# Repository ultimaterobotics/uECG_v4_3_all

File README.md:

# uECG
uECG - very small wearable ECG device that sends raw and processed data over BLE

**This is an old repository - new version is located here: https://github.com/ultimaterobotics/uECG (and is divided into multiple repositories for relevant parts of the project, links are in description)**

Project is in active development stage, at the current moment we have shared:
 * schematics and PCB design
 * ECG monitor program based on Node.js, cross-platform
 * ECG monitor program for Linux (outdated: might not work properly, please use cross-platform version instead)
 * Firmware for the main unit, rather stable and reliable build. Next planned major update will cover better beat detection and more robust bpm processing. 
 * Firmware for the base unit that supports uploading uECG firmware via radio
 * Android app with major rework, quite stable now
 * bootloader code for USB base station: supports base firmware update via USB without the need of STLink programmer
 * bootloader code for uECG device: supports firmware update via radio (requires base with new firmware, old base firmware doesn't support this function)

You can follow the project on Hackaday: https://hackaday.io/project/164486-uecg-a-very-small-wearable-ecg

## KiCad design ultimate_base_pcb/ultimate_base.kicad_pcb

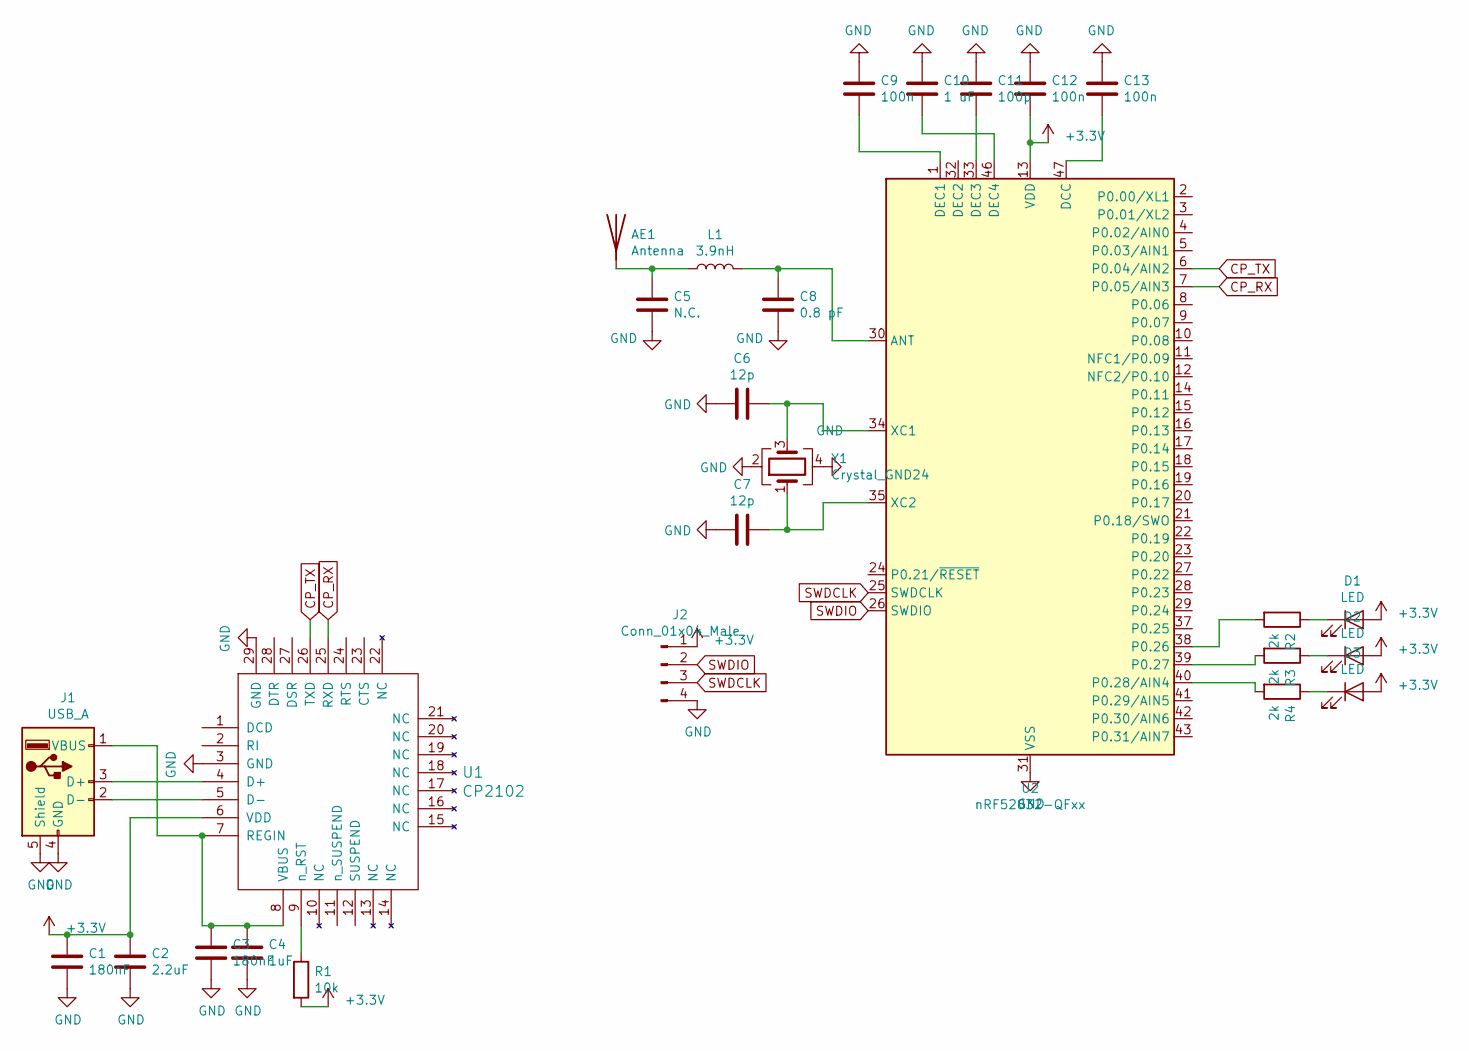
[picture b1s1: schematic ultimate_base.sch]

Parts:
AE1: Antenna; Texas_SWRA117D_2.4GHz_Left
C1, C3: 180nF; C_0402_1005Metric
C2: 2.2uF; C_0402_1005Metric
C4: 1uF; C_0402_1005Metric
C5: N.C.; C_0402_1005Metric
C6, C7: 12p; C_0402_1005Metric
C8: 0.8 pF; C_0402_1005Metric
C9, C12, C13: 100n; C_0402_1005Metric
C10: 1 uF; C_0402_1005Metric
C11: 100p; C_0402_1005Metric
D1, D2, D3: LED; LED_0603_1608Metric
J1: USB_A; conn_usb_A_china
J2: Conn_01x04_Male; PinHeader_1x04_P2.54mm_Horizontal
L1: 3.9nH; L_0402_1005Metric
R1: 10k; R_0402_1005Metric
R2, R3, R4: 2k; R_0402_1005Metric
U1: CP2102; QFN-28-1EP_5x5mm_P0.5mm_EP3.35x3.35mm
U2: nRF52832-QFxx; QFN-48-1EP_6x6mm_Pitch0.4mm
Y1: Crystal_GND24; Crystal_SMD_2520-4pin_2.5x2.0mm

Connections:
+3V3: C1.1, C2.1, C12.1, D1.2 (A), D2.2 (A), D3.2 (A), J2.1, R1.2, U1.6 (VDD), U2.13 (VDD), U2.36 (VDD), U2.48 (VDD)
CP_RX: U1.25 (RXD), U2.7 (P0.05/AIN3)
CP_TX: U1.26 (TXD), U2.6 (P0.04/AIN2)
GND: AE1.2, C1.2, C2.2, C3.2, C4.2, C5.2, C6.1, C7.1, C8.2, C9.2, C10.2, C11.2, C12.2, C13.2, J1.4 (GND), J1.5 (Shield), J2.4, U1.3 (GND), U1.29 (GND), U2.31 (VSS), U2.45 (VSS), U2.49 (VSS), Y1.2, Y1.4
unnamed: AE1.1, C5.1, L1.1
unnamed: C3.1, C4.1, J1.1 (VBUS), U1.7 (REGIN), U1.8 (VBUS)
unnamed: C6.2, U2.34 (XC1), Y1.3
unnamed: C7.2, U2.35 (XC2), Y1.1
unnamed: C8.1, L1.2, U2.30 (ANT)
unnamed: C9.1, U2.1 (DEC1)
unnamed: C10.1, U2.46 (DEC4)
unnamed: C11.1, U2.33 (DEC3)
unnamed: C13.1, U2.47 (DCC)
unnamed: D1.1 (K), R2.1
unnamed: D2.1 (K), R3.1
unnamed: D3.1 (K), R4.1
unnamed: J1.2 (D-), U1.5 (D-)
unnamed: J1.3 (D+), U1.4 (D+)
unnamed: R1.1, U1.9 (n_RST)
unnamed: R2.2, U2.38 (P0.26)
unnamed: R3.2, U2.39 (P0.27)
unnamed: R4.2, U2.40 (P0.28/AIN4)
SWDCLK: J2.3, U2.25 (SWDCLK)
SWDIO: J2.2, U2.26 (SWDIO)

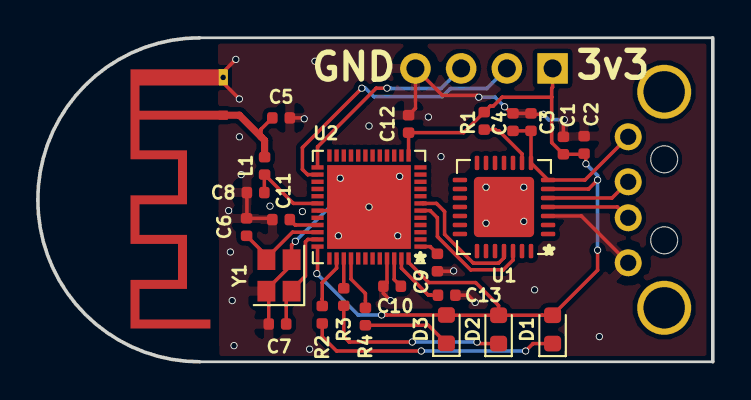
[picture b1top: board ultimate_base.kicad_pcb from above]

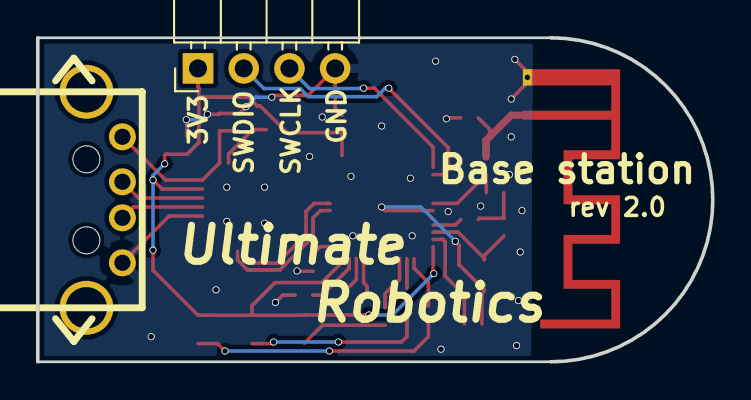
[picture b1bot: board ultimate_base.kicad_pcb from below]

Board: 2 copper layers, 37.5 x 18.0 mm, 27 parts (2 on the bottom side), 24 nets.

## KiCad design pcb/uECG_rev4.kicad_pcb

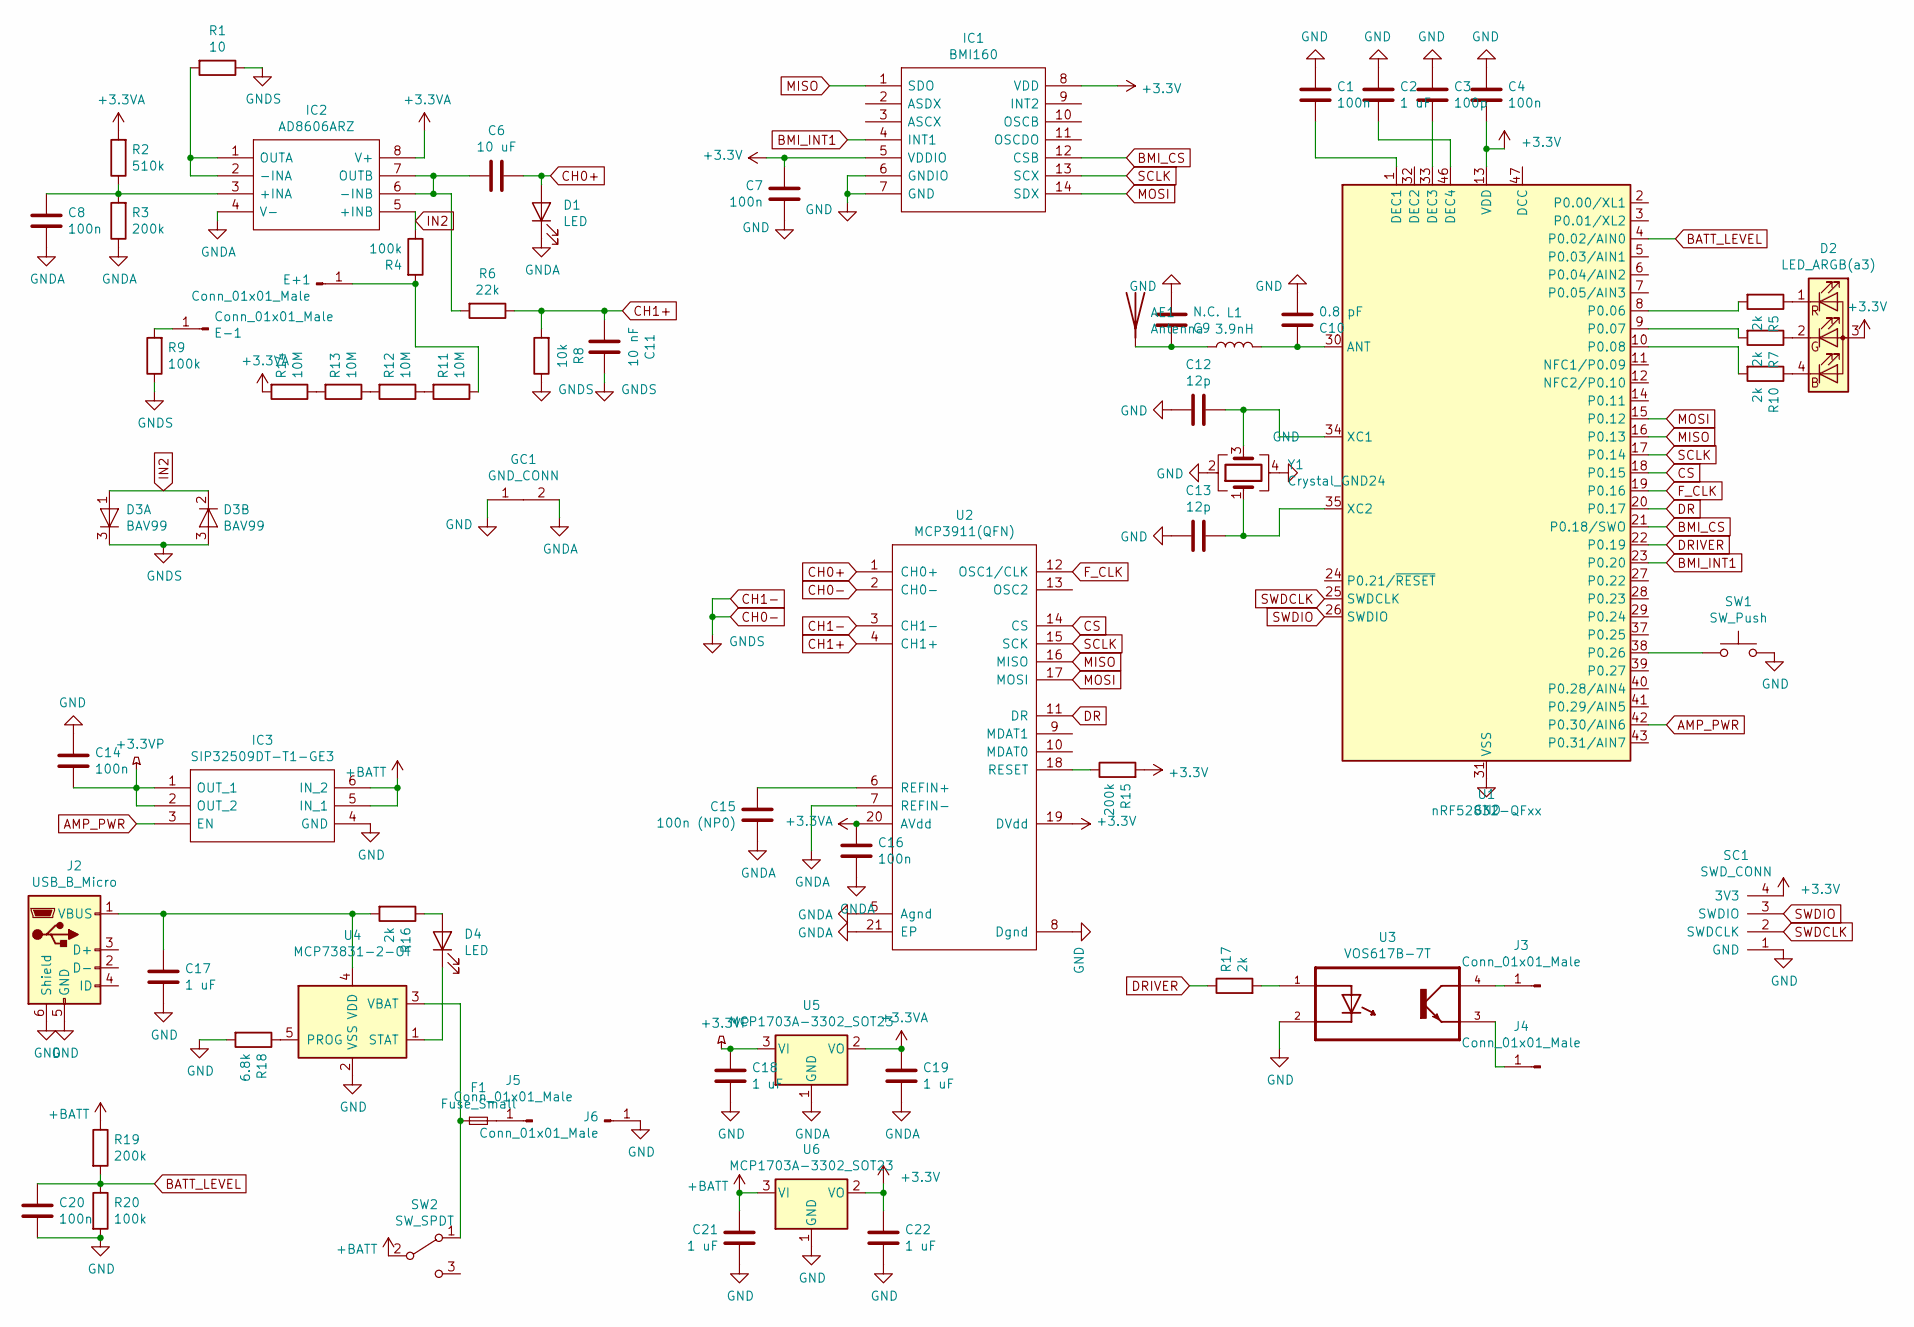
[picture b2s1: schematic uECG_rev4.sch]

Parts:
AE1: Antenna; Texas_SWRA117D_2.4GHz_Left
C1, C4, C7, C8, C14, C16, C20: 100n; C_0402_1005Metric
C2, C17, C18, C19, C21, C22: 1 uF; C_0402_1005Metric
C3: 100p; C_0402_1005Metric
C6: 10 uF; C_0603_1608Metric
C9: N.C.; C_0402_1005Metric
C10: 0.8 pF; C_0402_1005Metric
C11: 10 nF; C_0402_1005Metric
C12, C13: 12p; C_0402_1005Metric
C15: 100n (NP0); C_0402_1005Metric
D1, D4: LED; LED_0402_1005Metric
D2: LED_ARGB(a3); LED_RGB_0603
D3: BAV99; SOT-23
E+1: Conn_01x01_Male; PinHeader_1x01_P2.54mm_Vertical
E-1: Conn_01x01_Male; PinHeader_1x01_P2.54mm_Vertical
F1: Fuse_Small; Fuse_0603_1608Metric
GC1: GND_CONN
IC1: BMI160; PQFN50P300X250X88-14N; Manufacturer_Part_Number BMI160; Mouser Part Number 262-BMI160
IC2: AD8606ARZ; MSOP-8_3x3mm_P0.65mm; Manufacturer_Part_Number AD8606ARZ; Mouser Part Number 584-AD8606ARZ
IC3: SIP32509DT-T1-GE3; SOT95P284X110-6N; Manufacturer_Part_Number SIP32509DT-T1-GE3
J2: USB_B_Micro; conn_usb_B_micro_smd_our
J3, J5: Conn_01x01_Male; Pin_Header_Straight_1x01_Pitch2.54mm
J4, J6: Conn_01x01_Male; PinHeader_1x01_P2.54mm_Vertical
L1: 3.9nH; L_0402_1005Metric
R1: 10; R_0402_1005Metric
R2: 510k; R_0402_1005Metric
R3, R15, R19: 200k; R_0402_1005Metric
R4, R9, R20: 100k; R_0402_1005Metric
R5, R7, R10, R16, R17: 2k; R_0402_1005Metric
R6: 22k; R_0402_1005Metric
R8: 10k; R_0402_1005Metric
R11, R12, R13, R14: 10М; R_0402_1005Metric
R18: 6.8k; R_0402_1005Metric
SC1: SWD_CONN; SWD_CONNECTOR
SW1: SW_Push; SW_SPST_B3U-1000P
SW2: SW_SPDT; Slider_Switch_ali
U1: nRF52832-QFxx; QFN-48-1EP_6x6mm_Pitch0.4mm
U2: MCP3911(QFN); QFN-20-1EP_4x4mm_P0.5mm_EP2.5x2.5mm
U3: VOS617B-7T; SOIC127P700X210-4N
U4: MCP73831-2-OT; SOT-23-5
U5, U6: MCP1703A-3302_SOT23; SOT-23
Y1: Crystal_GND24; Crystal_SMD_2520-4pin_2.5x2.0mm

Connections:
+3.3VA: C16.2, C19.2, IC2.8 (V+), R2.2, R14.2, U2.20 (AVdd), U5.2 (VO)
+3.3VP: C14.1, C18.2, IC3.1 (OUT_1), IC3.2 (OUT_2), U5.3 (VI)
+3V3: C4.1, C7.2, C22.2, D2.3 (A), IC1.5 (VDDIO), IC1.8 (VDD), R15.2, SC1.4 (3V3), U1.13 (VDD), U1.36 (VDD), U1.48 (VDD), U2.19 (DVdd), U6.2 (VO)
+BATT: C21.2, IC3.5 (IN_1), IC3.6 (IN_2), R19.1, SW2.2 (B), U6.3 (VI)
AMP_PWR: IC3.3 (EN), U1.42 (P0.30/AIN6)
BATT_LEVEL: C20.2, R19.2, R20.1, U1.4 (P0.02/AIN0)
BMI_CS: IC1.12 (CSB), U1.21 (P0.18/SWO)
BMI_INT1: IC1.4 (INT1), U1.23 (P0.20)
CH0+: C6.2, D1.2 (A), U2.1 (CH0+)
CH0-: C11.2, D3.3 (K), R1.1, R8.1, R9.1, U2.2 (CH0-), U2.3 (CH1-)
CH1+: C11.1, R6.1, R8.2, U2.4 (CH1+)
CS: U1.18 (P0.15), U2.14 (CS)
DR: U1.20 (P0.17), U2.11 (DR)
DRIVER: R17.1, U1.22 (P0.19)
F_CLK: U1.19 (P0.16), U2.12 (OSC1/CLK)
GND: AE1.2, C1.2, C2.2, C3.2, C4.2, C7.1, C9.2, C10.2, C12.1, C13.1, C14.2, C17.1, C18.1, C20.1, C21.1, C22.1, GC1.1, IC1.6 (GNDIO), IC1.7 (GND), IC3.4 (GND), J2.5 (GND), J2.6 (Shield), J6.1, R18.2, R20.2, SC1.1 (GND), SW1.2, U1.31 (VSS), U1.45 (VSS), U1.49 (VSS), U2.8 (Dgnd), U3.2 (C), U4.2 (VSS), U6.1 (GND), Y1.2, Y1.4
GNDA: C8.1, C15.1, C16.1, C19.1, D1.1 (K), GC1.2, IC2.4 (V-), R3.1, U2.5 (Agnd), U2.7 (REFIN-), U2.21 (EP), U5.1 (GND)
IN2: D3.1 (A), D3.2 (K), IC2.5 (+INB), R4.1
MISO: IC1.1 (SDO), U1.16 (P0.13), U2.16 (MISO)
MOSI: IC1.14 (SDX), U1.15 (P0.12), U2.17 (MOSI)
unnamed: AE1.1, C9.1, L1.1
unnamed: C1.1, U1.1 (DEC1)
unnamed: C2.1, U1.46 (DEC4)
unnamed: C3.1, U1.33 (DEC3)
unnamed: C6.1, IC2.6 (-INB), IC2.7 (OUTB), R6.2
unnamed: C8.2, IC2.3 (+INA), R2.1, R3.2
unnamed: C10.1, L1.2, U1.30 (ANT)
unnamed: C12.2, U1.34 (XC1), Y1.3
unnamed: C13.2, U1.35 (XC2), Y1.1
unnamed: C15.2, U2.6 (REFIN+)
unnamed: C17.2, J2.1 (VBUS), R16.2, U4.4 (VDD)
unnamed: D2.1 (RK), R5.1
unnamed: D2.2 (GK), R7.1
unnamed: D2.4 (BK), R10.1
unnamed: D4.1 (K), U4.1 (STAT)
unnamed: D4.2 (A), R16.1
unnamed: E+1.1, R4.2, R11.1
unnamed: E-1.1, R9.2
unnamed: F1.1, SW2.1 (A), U4.3 (VBAT)
unnamed: F1.2, J5.1
unnamed: IC2.1 (OUTA), IC2.2 (-INA), R1.2
unnamed: J3.1, U3.4 (CO)
unnamed: J4.1, U3.3 (E)
unnamed: R5.2, U1.8 (P0.06)
unnamed: R7.2, U1.9 (P0.07)
unnamed: R10.2, U1.10 (P0.08)
unnamed: R11.2, R12.1
unnamed: R12.2, R13.1
unnamed: R13.2, R14.1
unnamed: R15.1, U2.18 (RESET)
unnamed: R17.2, U3.1 (A)
unnamed: R18.1, U4.5 (PROG)
unnamed: SW1.1, U1.38 (P0.26)
SCLK: IC1.13 (SCX), U1.17 (P0.14), U2.15 (SCK)
SWDCLK: SC1.2 (SWDCLK), U1.25 (SWDCLK)
SWDIO: SC1.3 (SWDIO), U1.26 (SWDIO)

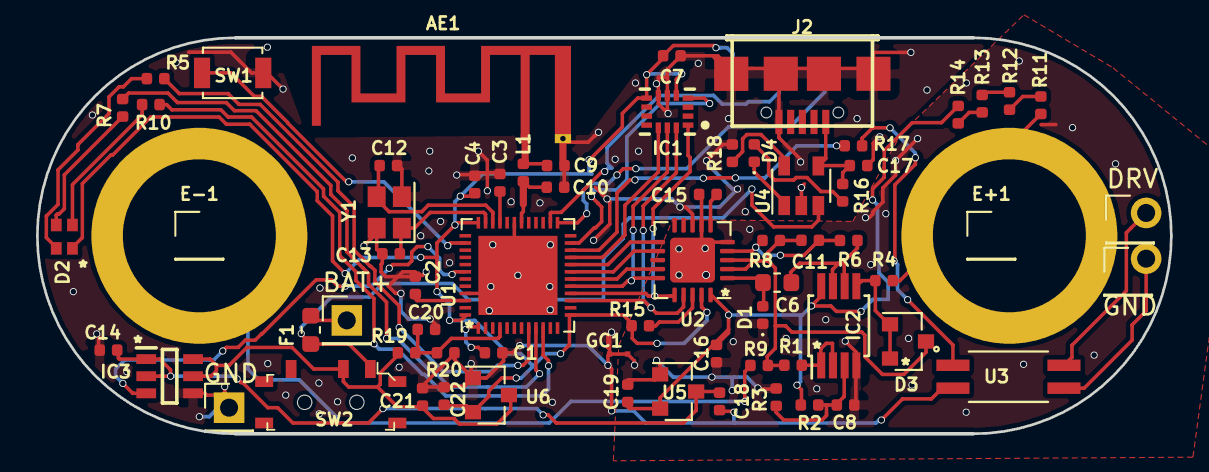
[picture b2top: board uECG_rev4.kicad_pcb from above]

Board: 2 copper layers, 63.0 x 22.0 mm, 69 parts (1 on the bottom side), 56 nets.

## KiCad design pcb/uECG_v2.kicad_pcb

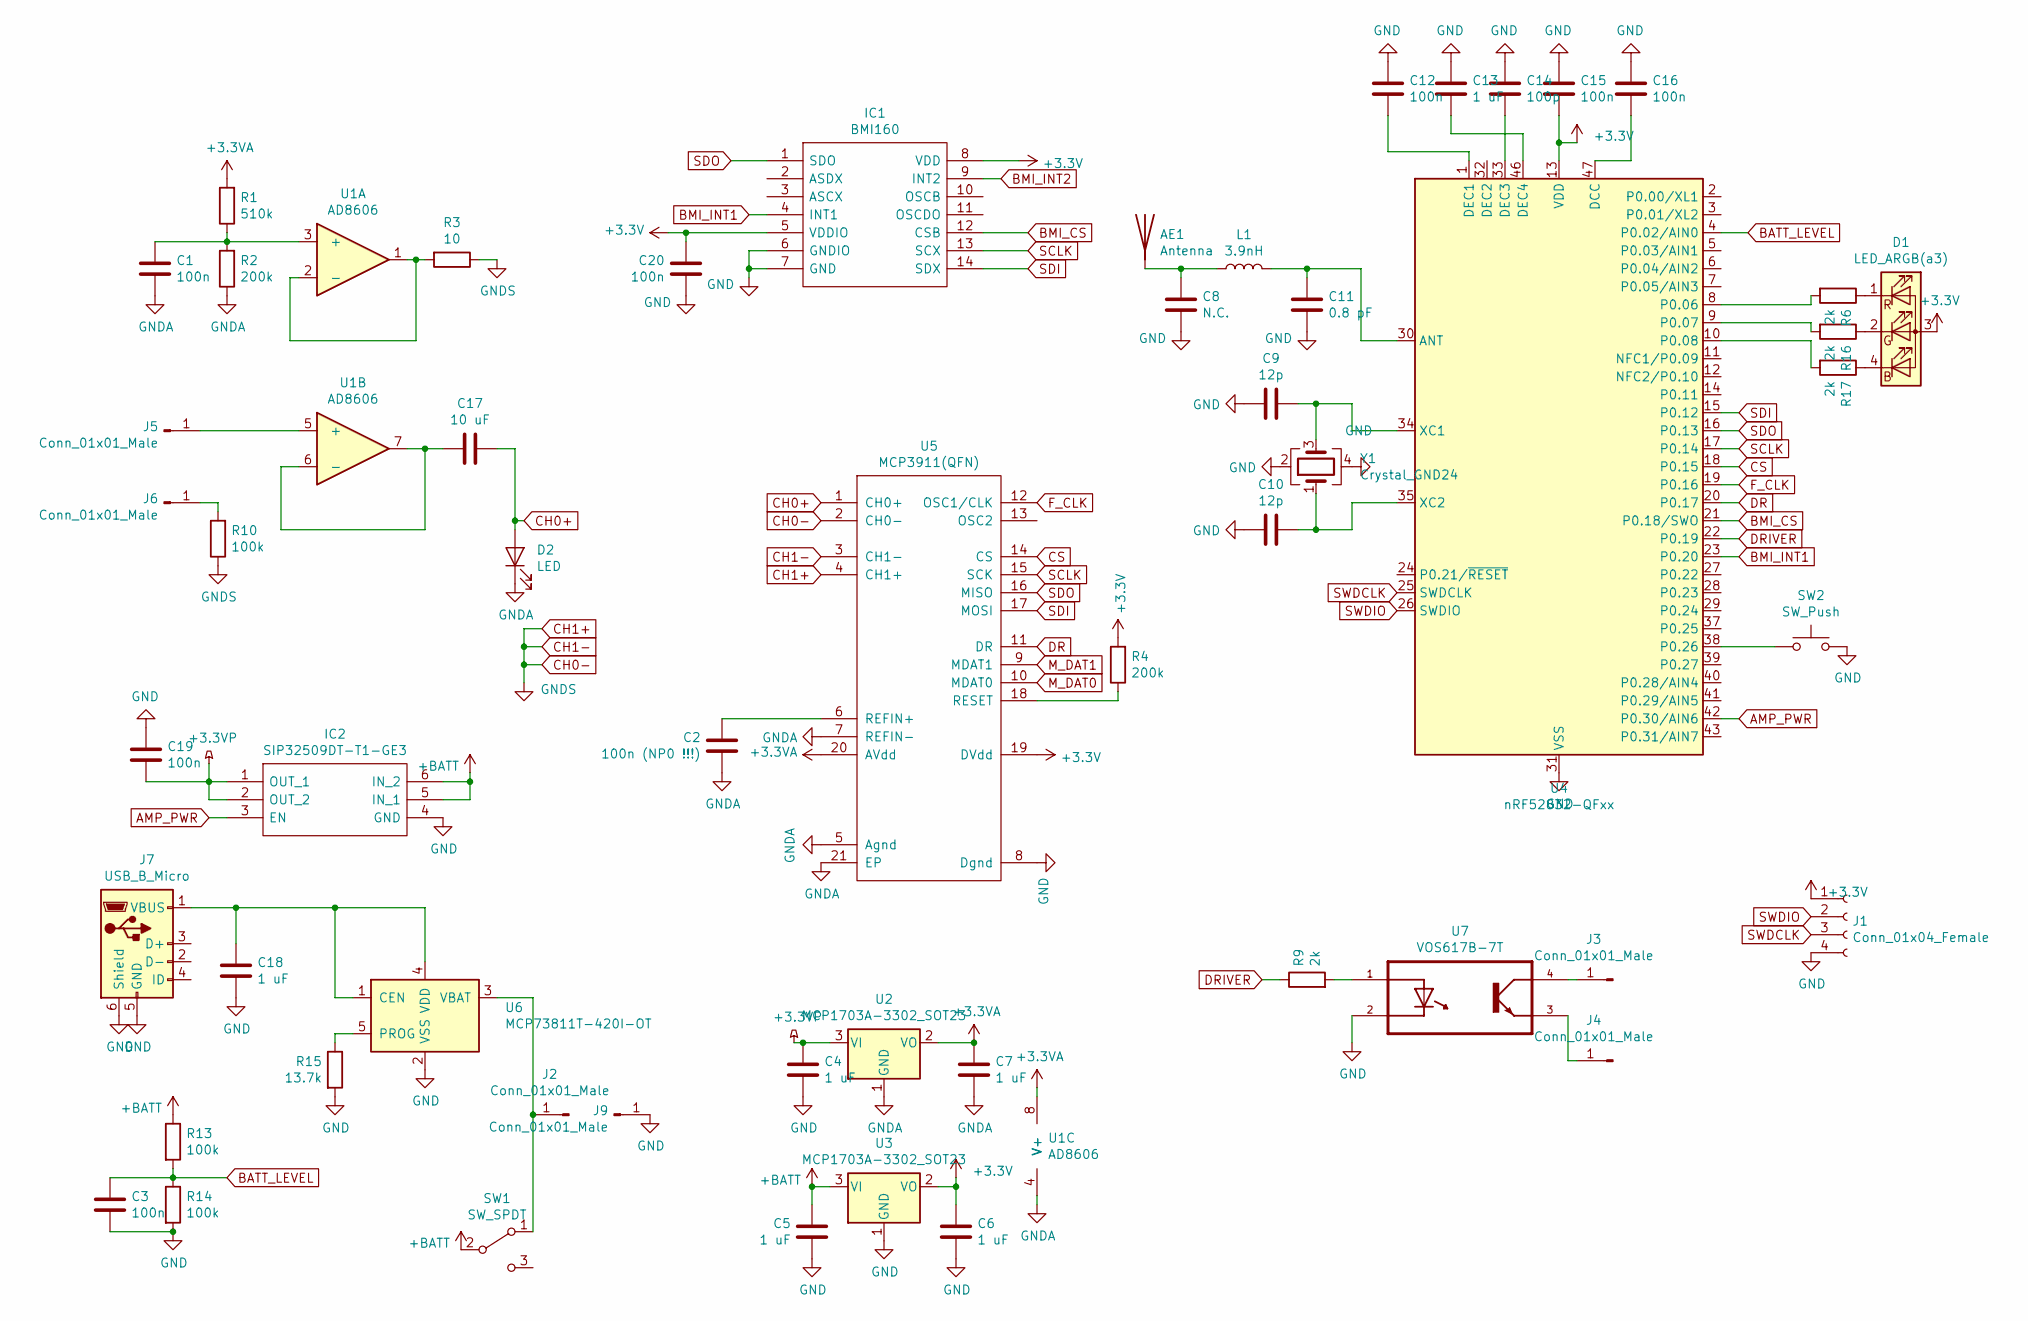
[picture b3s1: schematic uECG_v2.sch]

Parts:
AE1: Antenna; Texas_SWRA117D_2.4GHz_Left
C1, C3, C12, C15, C16, C19, C20: 100n; C_0402_NoSilk
C2: 100n (NP0 !!!); C_0402_NoSilk
C4, C5, C6, C7, C13, C18: 1 uF; C_0402_NoSilk
C8: N.C.; C_0402_NoSilk
C9, C10: 12p; C_0402_NoSilk
C11: 0.8 pF; C_0402_NoSilk
C14: 100p; C_0402_NoSilk
C17: 10 uF; C_0603
D1: LED_ARGB(a3); LED_RGB_0603
D2: LED; LED_0402
IC1: BMI160; PQFN50P300X250X88-14N; Manufacturer_Part_Number BMI160; Mouser Part Number 262-BMI160
IC2: SIP32509DT-T1-GE3; SOT95P284X110-6N; Manufacturer_Part_Number SIP32509DT-T1-GE3
J1: Conn_01x04_Female; Pin_Header_Straight_1x04_Pitch1.27mm_SMD_Pin1Left
J2, J3, J5, J6, J9: Conn_01x01_Male; Pin_Header_Straight_1x01_Pitch2.54mm
J4: Conn_01x01_Male; PinHeader_1x01_P2.54mm_Vertical
J7: USB_B_Micro; conn_usb_B_micro_smd_our
L1: 3.9nH; L_0402_1005Metric
R1: 510k; R_0402_NoSilk
R2, R4: 200k; R_0402_NoSilk
R3: 10; R_0402_NoSilk
R6, R9, R16, R17: 2k; R_0402_NoSilk
R10, R13, R14: 100k; R_0402_NoSilk
R15: 13.7k; R_0402_NoSilk
SW1: SW_SPDT; Slider_Switch_ali
SW2: SW_Push; SW_SPST_B3U-1000P
U1: AD8606; MSOP-8_3x3mm_Pitch0.65mm
U2, U3: MCP1703A-3302_SOT23; SOT-23
U4: nRF52832-QFxx; QFN-48-1EP_6x6mm_Pitch0.4mm
U5: MCP3911(QFN); QFN55P400X400X100-21N-D
U6: MCP73811T-420I-OT; SOT-23-5
U7: VOS617B-7T; SOIC127P700X210-4N
Y1: Crystal_GND24; Crystal_SMD_2520-4pin_2.5x2.0mm

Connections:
+3.3VA: C7.2, R1.2, U1.8 (V+), U2.2 (VO), U5.20 (AVdd)
+3.3VP: C4.2, C19.1, IC2.1 (OUT_1), IC2.2 (OUT_2), U2.3 (VI)
+3V3: C6.2, C15.1, C20.2, D1.3 (A), IC1.5 (VDDIO), IC1.8 (VDD), J1.1, R4.2, U3.2 (VO), U4.13 (VDD), U4.36 (VDD), U4.48 (VDD), U5.19 (DVdd)
+BATT: C5.2, IC2.5 (IN_1), IC2.6 (IN_2), R13.1, SW1.2 (B), U3.3 (VI)
AMP_PWR: IC2.3 (EN), U4.42 (P0.30/AIN6)
BATT_LEVEL: C3.2, R13.2, R14.1, U4.4 (P0.02/AIN0)
BMI_CS: IC1.12 (CSB), U4.21 (P0.18/SWO)
BMI_INT1: IC1.4 (INT1), U4.23 (P0.20)
BMI_INT2: IC1.9 (INT2)
CH0+: C17.2, D2.2 (A), U5.1 (CH0+)
CH0-: R3.1, R10.1, U5.2 (CH0-), U5.3 (CH1-), U5.4 (CH1+)
CS: U4.18 (P0.15), U5.14 (CS)
DR: U4.20 (P0.17), U5.11 (DR)
DRIVER: R9.1, U4.22 (P0.19)
F_CLK: U4.19 (P0.16), U5.12 (OSC1/CLK)
GND: AE1.2, C3.1, C4.1, C5.1, C6.1, C8.2, C9.1, C10.1, C11.2, C12.2, C13.2, C14.2, C15.2, C16.2, C18.1, C19.2, C20.1, IC1.6 (GNDIO), IC1.7 (GND), IC2.4 (GND), J1.4, J7.5 (GND), J7.6 (Shield), J9.1, R14.2, R15.2, SW2.2, U3.1 (GND), U4.31 (VSS), U4.45 (VSS), U4.49 (VSS), U5.8 (Dgnd), U6.2 (VSS), U7.2 (C), Y1.2, Y1.4
GNDA: C1.1, C2.1, C7.1, D2.1 (K), R2.1, U1.4 (V-), U2.1 (GND), U5.5 (Agnd), U5.7 (REFIN-), U5.21 (EP)
M_DAT0: U5.10 (MDAT0)
M_DAT1: U5.9 (MDAT1)
unnamed: AE1.1, C8.1, L1.1
unnamed: C1.2, R1.1, R2.2, U1.3 (+)
unnamed: C2.2, U5.6 (REFIN+)
unnamed: C9.2, U4.34 (XC1), Y1.3
unnamed: C10.2, U4.35 (XC2), Y1.1
unnamed: C11.1, L1.2, U4.30 (ANT)
unnamed: C12.1, U4.1 (DEC1)
unnamed: C13.1, U4.46 (DEC4)
unnamed: C14.1, U4.33 (DEC3)
unnamed: C16.1, U4.47 (DCC)
unnamed: C17.1, U1.6 (-), U1.7
unnamed: C18.2, J7.1 (VBUS), U6.1 (CEN), U6.4 (VDD)
unnamed: D1.1 (RK), R6.1
unnamed: D1.2 (GK), R16.1
unnamed: D1.4 (BK), R17.1
unnamed: J2.1, SW1.1 (A), U6.3 (VBAT)
unnamed: J3.1, U7.4 (CO)
unnamed: J4.1, U7.3 (E)
unnamed: J5.1, U1.5 (+)
unnamed: J6.1, R10.2
unnamed: R3.2, U1.1, U1.2 (-)
unnamed: R4.1, U5.18 (RESET)
unnamed: R6.2, U4.8 (P0.06)
unnamed: R9.2, U7.1 (A)
unnamed: R15.1, U6.5 (PROG)
unnamed: R16.2, U4.9 (P0.07)
unnamed: R17.2, U4.10 (P0.08)
unnamed: SW2.1, U4.38 (P0.26)
SCLK: IC1.13 (SCX), U4.17 (P0.14), U5.15 (SCK)
SDI: IC1.14 (SDX), U4.15 (P0.12), U5.17 (MOSI)
SDO: IC1.1 (SDO), U4.16 (P0.13), U5.16 (MISO)
SWDCLK: J1.3, U4.25 (SWDCLK)
SWDIO: J1.2, U4.26 (SWDIO)

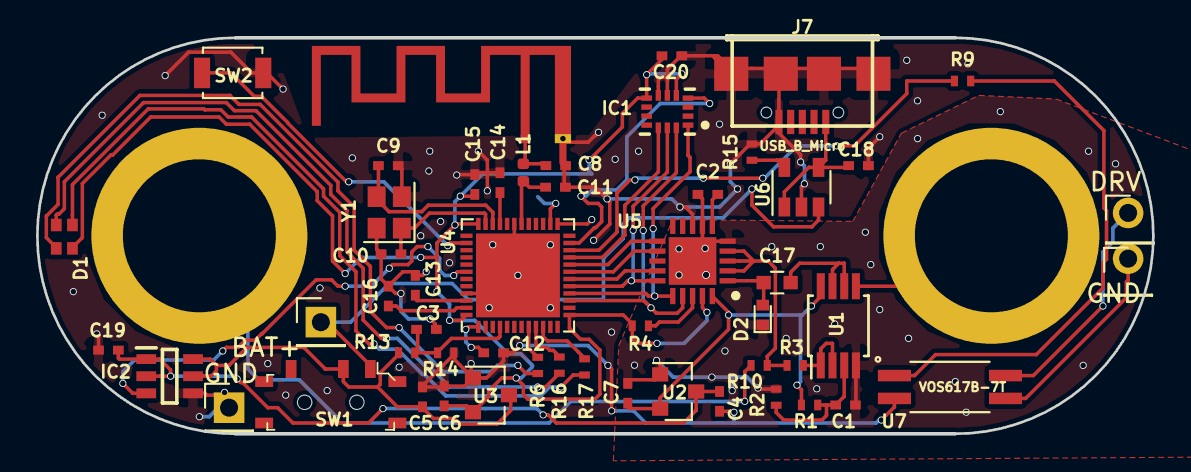
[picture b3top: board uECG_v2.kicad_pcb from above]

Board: 2 copper layers, 62.0 x 22.0 mm, 56 parts (1 on the bottom side), 49 nets.

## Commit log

2019-04-06 initial PCB design commit
2019-04-06 added rendered schematics and 3D view
2019-07-31 ECG monitor first version
2019-08-15 updated to PCB version 4
2019-08-17 Firmware for 4th PCB revision initial commit
2019-08-17 Firmware upload described
2019-08-17 Base station firmware initial commit
2019-08-17 Firmware readme created
2019-08-17 mentioned base firmware
2019-09-30 Android app added
2019-09-30 base unit PCB added
2019-09-30 Update README.md
    Firmware building instruction added
2020-02-06 major firmware update, fixed critical bug in BLE mode, improved communication protocol, also set of minor changes
2020-02-06 openocd is simpler to install now
2020-02-07 Update README.md
    updated firmware upload process
2020-02-07 BLE timing optimized
2020-02-08 ecg monitor significant update, implemented new data protocols, extracted BLE parsing into readable function (other parsing cases pending), added parsing of additional parameters
2020-02-13 Makefile updated
2020-02-17 removed old version
2020-02-17 added version 4.2
2020-02-17 critical bug in timing fixed
2020-02-18 direct mode version corrected
2020-02-18 added fix of received BPM and RR intervals from the device
2020-09-12 full rework of Android app - most of the code changed
2020-09-12 added bootloaders: USB bootloader for the base station and radio bootloader for uECG device, finally firmware update will be as simple as Arduino!
2020-09-12 uECG firware update for bootloader use: fixed multiple bugs, added temperature measurement, and built in a bootloader-compatible way. This firware version should be uploaded via bootloader instead of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
2020-09-12 Base firmware built for bootloader. Also added radio bootloading code, this version is meant to be uploaded using USB bootloader
2020-09-12 bugfix: using interrupt after VTOR update
2020-09-13 small bugfixes & recompiled binaries
2020-09-13 bugfix affecting nodejs interface compatibility, recompiled binaries
2020-09-21 PC app based on Node.js added
